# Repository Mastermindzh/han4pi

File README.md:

Han4pi is een groep enthousiaste studenten die samen met 1 leraar (Johan Korten) workshops organiseren met de Raspberry Pi microcomputer. Dit doen zij voor de Hogeschool van Arnhem en Nijmegen.

Gebruik een van de volgende links om door dit document te bladeren:

- [De installatie van het han4pi pakket](#user-content-install)
- [Raspbian installeren](#user-content-raspbian-install)
	- [Vervolginstructie voor Linux](#user-content-linux-raspbian-install)
	- [Vervolginstructie voor Windows](#user-content-windows-raspbian-install)
	- [Vervolginstructie voor Mac OS](#user-content-mac-raspbian-install)

**Organisatie:**

Voor eventuele vragen zijn alle projectleden laagdrempelig te mailen. U krijgt dan zo spoedig mogelijk reactie op uw vraag. Hieronder volgt een lijst met alle projectleden:

- Simon Baars -- simon.mailadres@gmail.com
- Johan Korten -- Johan.Korten@han.nl
- Rick van Lieshout -- Rick@mi-soft.nl
- Ron nabuurs -- nabuurs.ron@gmail.com
- Thomas Nobel -- thomas_nobel_2@hotmail.com

<div id = "install"></div>
## De installatie van het han4pi pakket
Voordat u het han4pi pakket kunt installeren zult u een sd kaartje moeten voorbereiden met de "RASPBIAN" software. U kunt de laatste versie van RASPBIAN downloaden op [deze](https://www.raspberrypi.org/downloads/raspbian/) website. Tevens is er een internetverbinding nodig voor de installatie.

1. Stel het root account in door de volgende commando's in de terminal te geven: <br />`sudo passwd root`<br /> En vervolgens tweemaal een root wachtwoord in te geven.

2. Klik linksboven in de hoek op "Menu" en kies voor "Shutdown". Uit het menu wat opspringt kiest u "Logout"

3. Log vervolgens in met de root account en open een terminal.

4. Geef vervolgens het volgende commando in: <br />`git clone https://github.com/Mastermindzh/han4pi.git`<br />

5. Open vervolgens het bestand "install.sh" met een teksteditor. Dit kan in de terminal bijv. met het commando: <br />`nano han4pi/install.sh`<br /> 

6. Pas de variabelen onder het kopje **#Gebruikers variabelen** aan zoals u wilt. Na het wijzigen van de variabelen drukt u op ctrl + x en vervolgens op y gevolgd door enter om het bestand op te slaan.

7. Daarna kunt u de installatie starten door het volgende commando te geven:<br />`bash han4pi/install.sh`

8. Volg de instructies op het scherm.
9. Herstart de raspberry pi met het `reboot` commando.

<div id = "raspbian-install"></div>
##Raspbian installeren

Om Raspbian te installeren heeft u een image nodig van het Raspbian OS. Om de laatste versie te downloaden klikt u [hier.](http://downloads.raspberrypi.org/raspbian_latest) Pak de zip uit door er met de rechtermuisknop op te drukken en te kiezen voor "uitpakken" of een dergelijke optie.

Als u het .zip bestand heeft uitgepakt kunt u hieronder verdergaan met de installatieinstructies die bij uw systeem passen.

<div id = "linux-raspbian-install"></div>
###Vervolginstructie voor Linux
Als eerste stap gaan we het pad naar het sd kaartje waar we Raspbian op installeren zoeken. Dit kunnen we doen door het volgende commando in de terminal in te geven:<br />`lsblk`<br />

U krijgt dan een venster met een aantal gegevens (onderstaande afbeelding). De belangrijkste gegevens hier zijn de "NAME" en "SIZE". Meestal is de "SIZE" kolom genoeg om uw sd kaartje te vinden. Dit omdat andere block apparaten (zoals een hdd) vaak veel groter zijn. Kunt u echter niet door alleen de kolom "SIZE" te gebruiken achterhalen welke regel uw sd kaartje betreft dan kunt u simpelweg de sd kaart eruit halen en dan het commando intypen. Vervolgens stopt u de sd kaart terug en voert u het commando nog eens uit. De verandering in het tweede resultaat is dan uw sd kaartje. Op de afbeelding hieronder is te zien dat mijn sd kaart op plek "sdc" zit.

Zodra u de regel van het sd kaartje heeft gevonden kijkt u bij de kolom "NAME". De naam zonder nummer is uw apparaat. In het voorbeeld hierboven is dit sdc omdat die als enige 8gb is (en de sd kaart is 8gb). Dat wil zeggen dat het apparaat zich op de locatie "/dev/sdc" bevindt.

U kunt nu middels het volgende commando de img op de sd kaart zetten. Let er dan wel op dat alle gegevens die nu op de sd kaart staan gewist zullen worden.<br />`sudo dd if=/pad/naar/het/.img/bestand of=/dev/sdc` <br />
Waar sdc de lettercombinatie is die u hierboven middels `lsblk` heeft gevonden.

Na het uitvoeren van het commando dient u te wachten tot het commando klaar is. Tot die tijd kunt u geen andere commando's in de terminal typen.
Als u de status wilt opvragen van de transactie opent u een tweede terminal en geeft u het volgende commando in `sudo kill -USR1 $(pidof dd)`

<div id = "windows-raspbian-install"></div>
###Vervolginstructie voor Windows

Als eerste stap moet het programma Win 32 Diskimager gedownload worden. klik [hier](http://sourceforge.net/projects/win32diskimager/files/latest/download) om dat te doen.
Nadat de installatie van het programma voltooid is kunt u het programma opstarten. Om het programma op te starten navigeert u naar "C:\Program Files (x86)\ImageWriter" (standaard installatie locatie) en dubbel klikt u op Win32DiskImager.exe.

Zodra het programma is gestart klikt u op het blauwe mapje en navigeert u naar het eerder gedownloade img bestand. Selecteer nu bij devices het sd kaartje waar Raspbian op geinstalleerd moet worden.
Klik vervolgens op "write" om raspbian om de sd kaart te installeren.

<div id = "mac-raspbian-install"></div>
###Vervolginstructie voor Mac OS
Als eerste stap gaan we het pad naar het sd kaartje waar we Raspbian op installeren zoeken. Dit kunnen we doen door het volgende commando in de terminal in te geven:<br />`diskutil list`<br />

U krijgt dan een venster met een aantal gegevens (onderstaande afbeelding). De belangrijkste gegevens hier zijn de "IDENTIFIER" en "SIZE". Meestal is de "SIZE" kolom genoeg om uw sd kaartje te vinden. Dit omdat andere block apparaten (zoals een hdd) vaak veel groter zijn. Kunt u echter niet door alleen de kolom "SIZE" te gebruiken achterhalen welke regel uw sd kaartje betreft dan kunt u simpelweg de sd kaart eruit halen en dan het commando intypen. Vervolgens stopt u de sd kaart terug en voert u het commando nog eens uit. De verandering in het tweede resultaat is dan uw sd kaartje. Op de afbeelding hieronder is te zien dat mijn sd kaart op plek "sdc" zit.

Vervolgens zal u de sd kaart moeten "unmounten" dit kunt u doen met het volgende commando: <br />`diskutil unmountDisk /dev/disk4`<br />
waar 'disk4' de "IDENTIFIER" is die u bij de vorige stap heeft gevonden.

U kunt nu middels het volgende commando de img op de sd kaart zetten. Let er dan wel op dat alle gegevens die nu op de sd kaart staan gewist zullen worden.<br />`sudo dd bs=1m if=/pad/naar/het/.img/bestand of=/dev/disk4` <br />
waar 'disk4' de "IDENTIFIER" is die u bij de vorige stap heeft gevonden.

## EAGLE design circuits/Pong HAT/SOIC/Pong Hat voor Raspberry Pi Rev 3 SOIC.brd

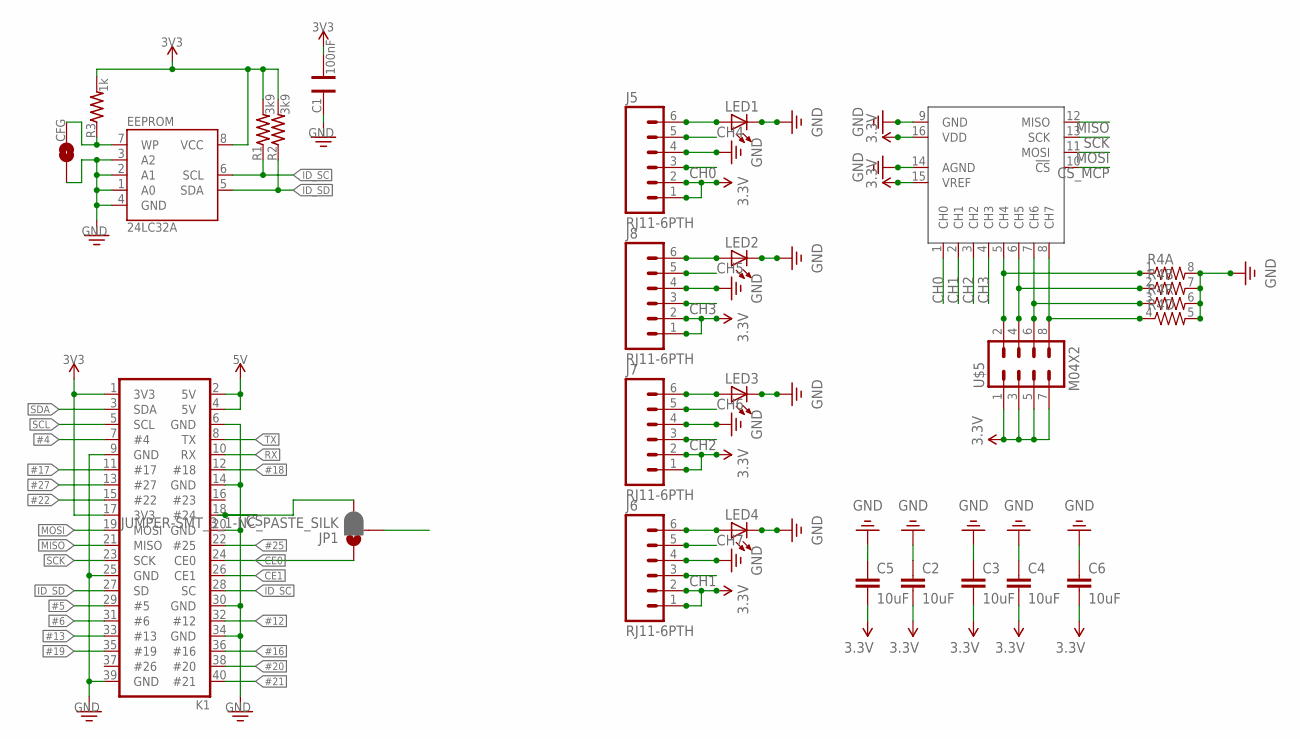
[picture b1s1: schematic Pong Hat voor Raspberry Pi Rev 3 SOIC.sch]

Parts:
C1: 100nF; CAP-0603
C2, C3, C4, C5, C6: 10uF; 0805
CFG: 1X02-SJ-NO
EEPROM: 24LC32A; SO08-EIAJ
J5, J6, J7, J8: RJ11-6PTH; RJ11-6
JP1: JUMPER-SMT_3_1-NC_PASTE_SILK; SMT-JUMPER_3_1-NC_PASTE_SILK
K1: 2X20-RPI-ALT
LED1, LED2, LED3, LED4: LEDCHIP-LED0805; CHIP-LED0805
R1, R2: 3k9; RES-0603; TOLERANCE 5%
R3: 1k; RES-0603; TOLERANCE 5%
R4: RESISTOR-ARRAY0603-ARV; 0603-ARV
U$5: M04X2; 2X4
U$7: MCP3008SL; SO16

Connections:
3.3V: C1.1, C2.2, C3.2, C4.2, C5.2, C6.2, EEPROM.8 (VCC), J5.1, J5.2, J6.1, J6.2, J7.1, J7.2, J8.1, J8.2, K1.1 (3V3), K1.17 (3V3), R1.2, R2.2, R3.2, U$5.1, U$5.3, U$5.5, U$5.7, U$7.15 (VREF), U$7.16 (VDD)
5V: K1.2 (5V), K1.4 (5V)
#4: K1.7 (#4)
#5: K1.29 (#5)
#6: K1.31 (#6)
#12: K1.32 (#12)
#13: K1.33 (#13)
#16: K1.36 (#16)
#17: K1.11 (#17)
#18: K1.12 (#18)
#19: K1.35 (#19)
#20: K1.38 (#20)
#21: K1.40 (#21)
#22: K1.15 (#22)
#25: K1.22 (#25)
#27: K1.13 (#27)
CE0: JP1.1, K1.24 (CE0)
CE1: K1.26 (CE1)
CH0: J5.3, U$7.1 (CH0)
CH1: J6.3, U$7.2 (CH1)
CH2: J7.3, U$7.3 (CH2)
CH3: J8.3, U$7.4 (CH3)
CH4: J5.5, R4.1, U$5.2, U$7.5 (CH4)
CH5: J8.5, R4.2 (1), U$5.4, U$7.6 (CH5)
CH6: J7.5, R4.3 (1), U$5.6, U$7.7 (CH6)
CH7: J6.5, R4.4 (1), U$5.8, U$7.8 (CH7)
CS: JP1.3, K1.18 (#24)
CS_MCP: JP1.2, U$7.10 (!CS)
GND: C1.2, C2.1, C3.1, C4.1, C5.1, C6.1, CFG.1, EEPROM.1 (A0), EEPROM.2 (A1), EEPROM.3 (A2), EEPROM.4 (GND), J5.4, J6.4, J7.4, J8.4, K1.6 (GND), K1.9 (GND), K1.14 (GND), K1.20 (GND), K1.25 (GND), K1.30 (GND), K1.34 (GND), K1.39 (GND), LED1.C, LED2.C, LED3.C, LED4.C, R4.5 (2), R4.6 (2), R4.7 (2), R4.8 (2), U$7.9 (GND), U$7.14 (AGND)
ID_SC: EEPROM.6 (SCL), K1.28 (SC), R1.1
ID_SD: EEPROM.5 (SDA), K1.27 (SD), R2.1
MISO: K1.21 (MISO), U$7.12 (MISO)
MOSI: K1.19 (MOSI), U$7.11 (MOSI)
unnamed: J8.6, LED2.A
unnamed: J7.6, LED3.A
unnamed: CFG.2, EEPROM.7 (WP), R3.1
unnamed: J6.6, LED4.A
unnamed: J5.6, LED1.A
RX: K1.10 (RX)
SCK: K1.23 (SCK), U$7.13 (SCK)
SCL: K1.5 (SCL)
SDA: K1.3 (SDA)
TX: K1.8 (TX)

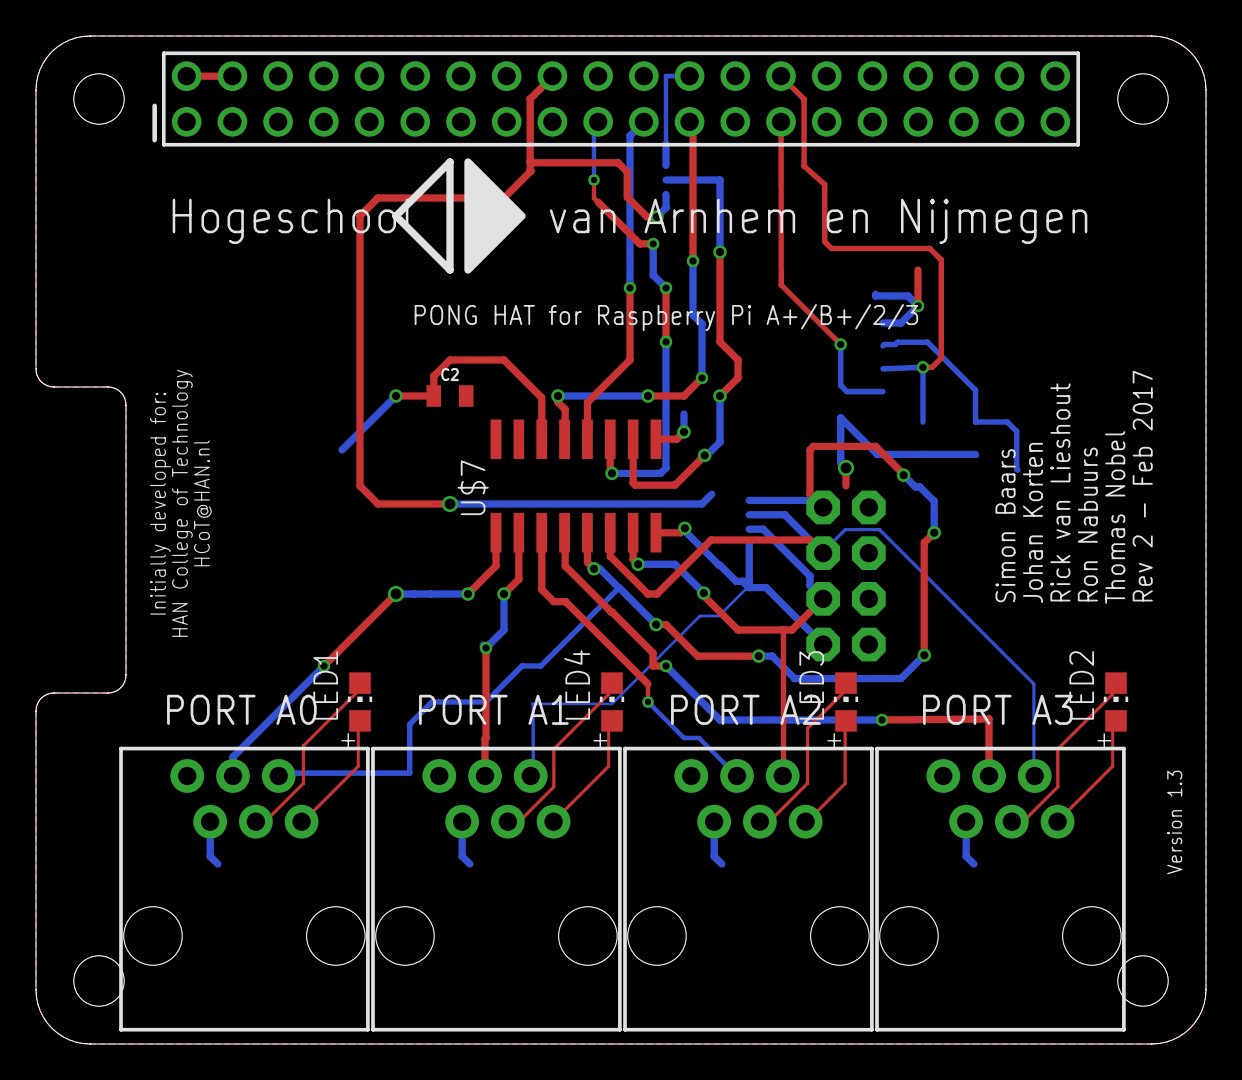
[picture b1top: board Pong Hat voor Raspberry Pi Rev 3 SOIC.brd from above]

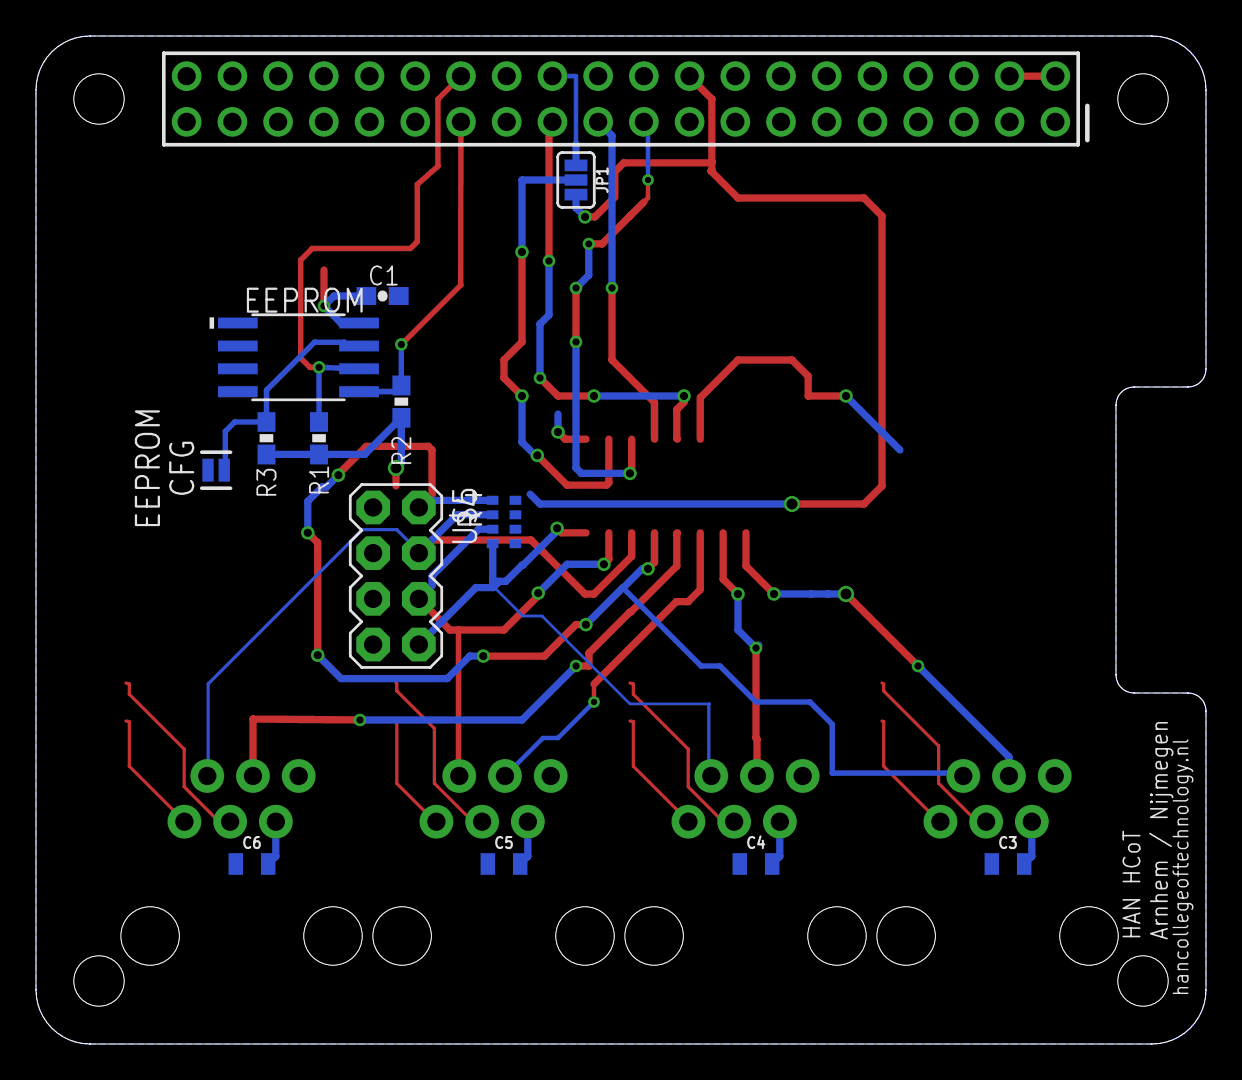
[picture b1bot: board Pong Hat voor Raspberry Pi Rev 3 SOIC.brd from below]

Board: 2 copper layers, 65.0 x 56.0 mm, 24 parts (13 on the bottom side), 24 nets.

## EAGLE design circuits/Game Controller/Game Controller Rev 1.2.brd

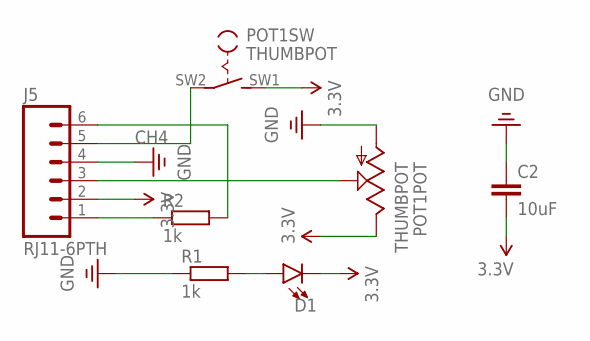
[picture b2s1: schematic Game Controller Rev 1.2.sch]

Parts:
C2: 10uF; 0805
D1: LED-3MM-NO_SILK; LED_3MM-NS
J5: RJ11-6PTH; RJ11-6
POT1: THUMBPOT; THUMBWHEEL
R1, R2: 1k; M0805

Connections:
3.3V: C2.2, D1.K (C), J5.2, POT1.3 (E), POT1.SW1 (S)
CH4: J5.5, POT1.SW2
GND: C2.1, J5.4, POT1.1 (A), R1.1
unnamed: D1.A, R1.2
unnamed: J5.3, POT1.2 (S)
unnamed: J5.6, R2.2
unnamed: J5.1, R2.1

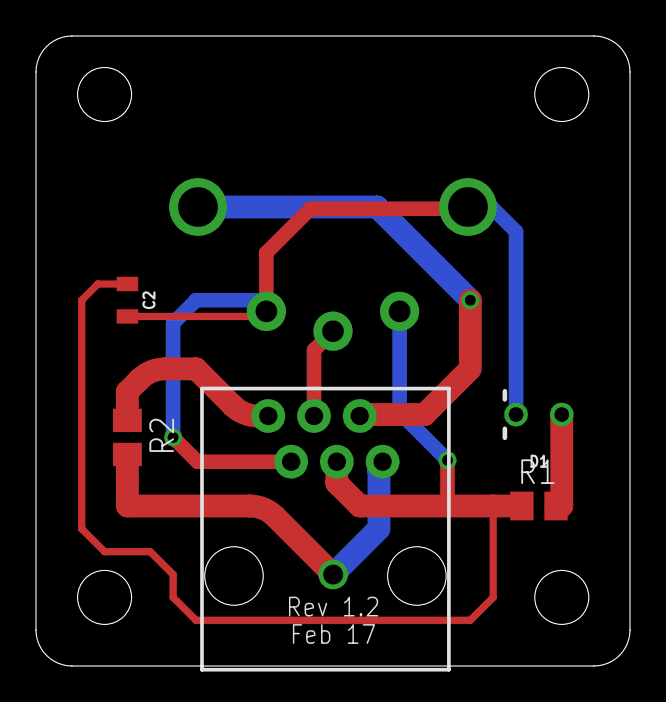
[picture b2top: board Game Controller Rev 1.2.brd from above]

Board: 2 copper layers, 33.0 x 35.0 mm, 6 parts (1 on the bottom side), 7 nets.

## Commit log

2015-10-07 Create Readme.md
    Added readme
2015-10-07 Added TheRealSimjoo as a collaborator and pushed my latest version
2015-10-07 folder creation
2015-10-07 reorganised readme, added han logo
2015-10-09 ascii art added
2015-10-12 Added a wallpaper and renamed initialize.sh to install.sh
2015-10-13 added parsing command line argument example
2015-10-20 added some images
2015-10-21 Controller designs uploaded and Logos uploaded
2015-10-23 added wallpaper and greeter.sh
2015-10-26 flags.sh added
2015-10-26 merged flags into install and added version checking
2015-10-26 testing update
2015-10-26 update function now skips logo
2015-10-26 added bash examples, loops is WIP
2015-10-29 Concept voor de uitwerking van de bal binnen het pongspel (voor thomas)
2015-10-29 Hoofdmenu voor pong
2015-10-30 Update LICENSE
2015-11-02 Menu aangepast
2015-11-02 En->Nl translations
2015-11-02 background changing added.
2015-11-02 wallpaper change
2015-11-03 Eerste (vrij vroege) versie van ponggit add ponggit add pong
2015-11-06 added network checking, username sanitizing and greeter script
2015-11-09 Installation tutorial in readme and modified the install script a bit. Installation now works perfectly fine!
2015-11-09 Added table of content to readme
2015-11-09 Testing readme layout
2015-11-09 playing with markdown
2015-11-09 spelen met markdown
2015-11-09 github markdown id fix
2015-11-10 added to install: keymap changing, system update, software installation, terminal autostart
2015-11-10 improved comments in install.sh and added checks for the useraccount. Also added a help menu
2015-11-11 Install script updates. new stuff works too now :)
2015-11-11 pong game nieuwe classes en methoden. Een methode werkt nog niet weet ook niet waarom.
2015-11-11 Readme, in the process of writing install instructions. testing the layout right now
2015-11-11 more layout testing
2015-11-11 added linux and mac tutorials
2015-11-11 Changed heading styles
2015-11-11 spelling and grammer check
2015-11-11 readme fix
2015-11-11 Nieuwe pong versie met klassen en werkend
2015-11-12 renames, pygame example and other stuff
2015-11-12 Uploaded windows tutorial for Ron Nabuurs. (he was too lazy to do so)
2015-11-12 added python examples
2015-11-12 volledig samengevoegde versie van pong met een paar nieuwe functionaliteiten toegevoegd. zit helaas nog een foutje in...
2015-11-16 Een aantal grote bugs zijn gefixt, en de code is vele male netjeser gemaakt
2015-11-17 nieuwste pong, nu helemaal af zonder geluid
2015-11-20 upload catch the raspberry
2015-11-20 Moved Controller laser designs
2015-11-20 Moved images folder on remote
2015-11-23 Handleiding ter behoeve van de game.
2015-11-23 pong, laatste versie
2015-11-23 adc code upload
2015-11-23 adc upload attempt 2
2015-11-24 Scratch Pong v1 added
2015-11-24 Catch the raspberry with controller support and fixed Kevin McLeod's name. Sorry Kevin :-)
2015-11-24 vnc server + added games to menu
2015-11-24 removed reboot
2015-11-24 changed whoami with mastermindzh and added vnc setup line (167)
2015-11-24 I am being stupid. removed reboot
2015-11-24 fixes
2015-11-25 Nieuwe geupdate handleiding voor han4pi (pong). Dit keer in .md formaat
2015-11-25 Nieuwe update voor spelhandleiding
2015-11-25 werkende pong
2015-11-26 Spi gefixt
2015-12-02 Contact formulier met de contactgegevens erin.
2015-12-02 Contact gegevens han4pi werkgroep.
2015-12-08 sanitization of install.sh and user permission changes.
2017-02-13 enable ssh, menu items don't work yet. Will fix soon
2017-02-13 temporarily added desktop icons for catch the raspberry
2017-02-18 Added test input python code
    Added test input python code for Pi hardware SPI with MCP3008
2017-02-18 Eagle PCB Files
    Eagle PCB Files
2017-02-21 pixel upgrade forces us to copy the wallpaper to two locations
2017-02-21 renaming dir
2017-02-22 Nieuwe spicode en een fout in de berekening van spelerposities opgelost
2017-02-22 Added gethan4pi for Simon
2017-02-22 Klein dingetje
2017-02-22 Update 00 - README.txt
    Spellings gerelateerde commit.
2017-02-22 Update 00 - README.txt
    Idem dito spellingsgerelateerde zaken.
2017-02-22 afstandsmeter toegevoegd
2017-02-22 Klein positioneringsfoutje opgelost
2017-02-22 voorlopig
2017-02-22 Refactoring en een fout gefixt
2017-02-22 afgemaakt
2017-02-22 bal refactor
2017-02-22 na overleg nutteloze changes ongedaan gemaakt
2017-02-22 snel
2017-02-23 Awesome code geschreven met de leerlingen tijdens de workshop op 23/02/2017
2017-02-23 ~Simon - meer code geschreven

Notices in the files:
parts and their libraries:
SparkFun: Licensing: CC v3.0 Share-Alike You are welcome to use this library for commercial purposes.
SparkFun-LED: Licensing: Creative Commons ShareAlike 4.0 International - https://creativecommons.org/licenses/by-sa/4.0
